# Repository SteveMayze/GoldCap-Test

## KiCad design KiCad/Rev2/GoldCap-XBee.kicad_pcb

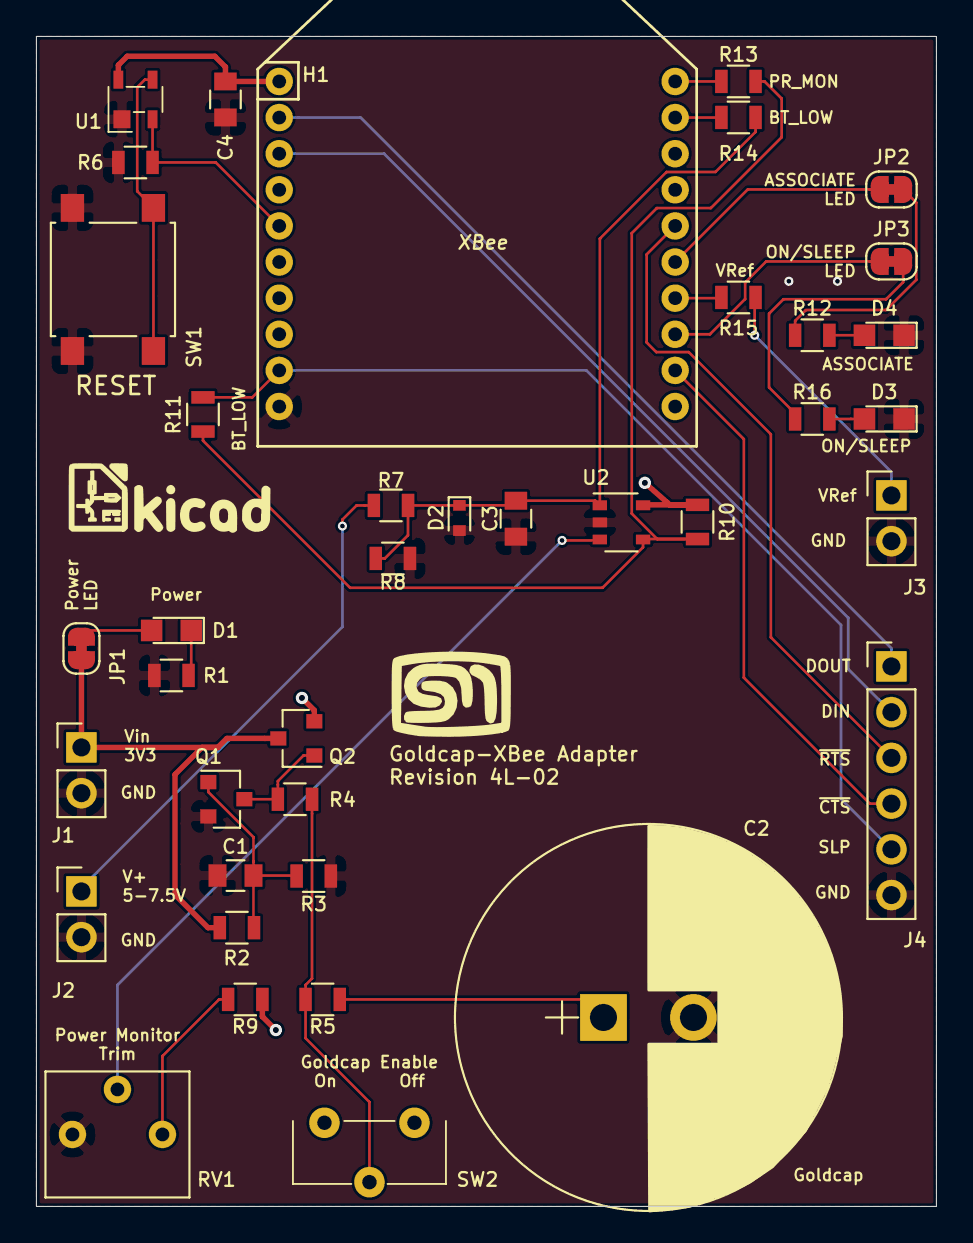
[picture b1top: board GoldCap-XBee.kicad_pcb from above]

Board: 4 copper layers, 50.0 x 65.0 mm, 39 parts (0 on the bottom side), 31 nets.

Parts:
C1, C3, C4: 100nF; C_0805
C2: 470mF 5V5; CP_Radial_D21.5mm_P5.00mm
D1, D3, D4: LED; LED_0805
D2: MM5Z3V3T1G; D_SOD-523
H1: DIGI_XBEE; XBEE_S2C
J1: 3V3 IN; Pin_Header_Straight_1x02_Pitch2.54mm
J2: 5-7.5V; Pin_Header_Straight_1x02_Pitch2.54mm
J3: VREF; Pin_Header_Straight_1x02_Pitch2.54mm
J4: Conn_01x06_Female; Pin_Header_Straight_1x06_Pitch2.54mm
JP1: Pwr LED; SolderJumper-2_P1.3mm_Bridged_RoundedPad1.0x1.5mm
JP2: ASSOCIATE_BR; SolderJumper-2_P1.3mm_Bridged_RoundedPad1.0x1.5mm
JP3: ON; SolderJumper-2_P1.3mm_Bridged_RoundedPad1.0x1.5mm
Q1: BC847; SOT-23
Q2: IRLML6401; SOT-23
R1, R12, R16: 680Ω; R_0805
R2: 470kΩ; R_0805
R3, R4, R6, R7, R8: 100kΩ; R_0805
R5: 33Ω; R_0805
R9, R11, R13, R14, R15: 0Ω; R_0805
R10: 10kΩ; R_0805
RV1: 10kΩ; Trimpot_CT6EP
SW1: Reset; SW_SPST_B3S-1000
SW2: SW_SPDT; SPST-CL-SB-12C01
U1: SGM811; SGM811B
U2: LMV331; SOT-25

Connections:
/ASSOCIATE: D4.2, R12.1
/ON: D3.2, R16.1
/PWR_MON: C3.1, D2.1, R7.2, R8.1, R14.1, U2.1
/SLEEP_REQ: H1.9, J4.5, R11.1
/VCC: C4.1, H1.1, Q2.2, R9.1, R10.1, SW2.1, U1.4, U2.5
/VIN_3V3: J1.1, JP1.1, Q2.3, R2.2
/VREF: J3.1, R15.1
/Vb: J2.1, R7.1
/Vref: RV1.2, U2.3
/XBEE_DIN: H1.3, J4.2
/XBEE_DOUT: H1.2, J4.1
/~BATT_LOW~: R10.2, R11.2, R13.1, U2.4
/~RESET: H1.5, R6.1, U1.2
/~XBEE_CTS: H1.12, J4.4
/~XBEE_RTS: H1.16, J4.3
GND: C1.2, C2.2, C3.2, C4.2, D2.2, D3.1, D4.1, H1.10, J1.2, J2.2, J3.2, J4.6, Q1.2, R1.2, R3.2, R6.2, R8.2, RV1.3, SW1.1, U1.1, U2.2
unnamed: C1.1, Q1.1, R2.1, R3.1
unnamed: C2.1, R5.2
unnamed: D1.1, R1.1
unnamed: D1.2, JP1.2
unnamed: H1.13, JP3.1
unnamed: H1.14, R15.2
unnamed: H1.15, JP2.1
unnamed: H1.19, R14.2
unnamed: H1.20, R13.2
unnamed: JP2.2, R12.2
unnamed: JP3.2, R16.2
unnamed: Q1.3, Q2.1, R4.1
unnamed: R4.2, R5.1, SW2.2
unnamed: R9.2, RV1.1
unnamed: SW1.2, U1.3

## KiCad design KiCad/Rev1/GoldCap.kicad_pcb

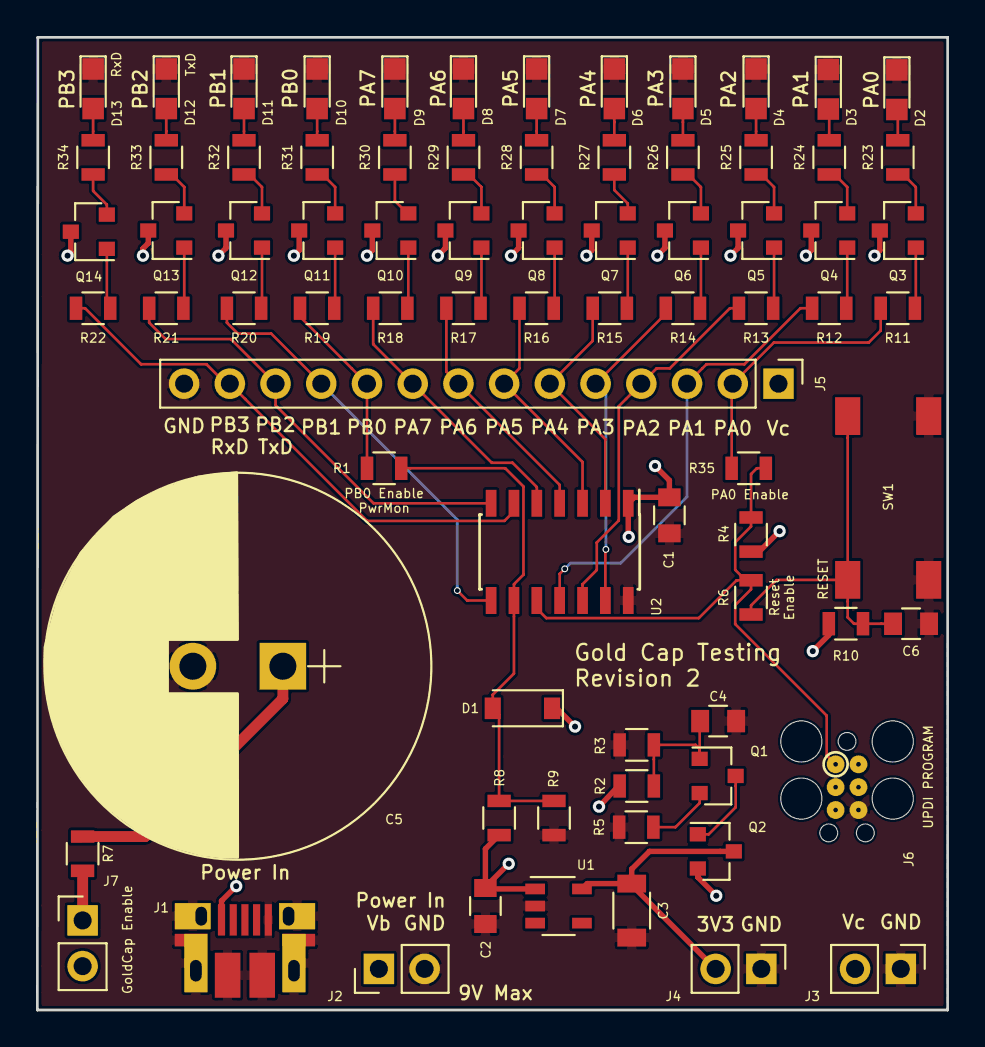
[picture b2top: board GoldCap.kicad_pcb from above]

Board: 2 copper layers, 50.6 x 54.0 mm, 78 parts (0 on the bottom side), 60 nets.

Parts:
C1, C4, C6: 100n; C_0805
C2: 1μF; C_0805
C3: 2.2μF; C_1206
C5: 470m 5V5; CP_Radial_D21.5mm_P5.00mm
D1: BAT43; D_SOD-123
D2, D3, D4, D5, D6, D7, D8, D9, D10, D11, D12, D13: LED; LED_0805
J1: USB_B_2.0_Micro
J2: Pwr In; Pin_Header_Straight_1x02_Pitch2.54mm
J3: Pwr Out; Pin_Header_Straight_1x02_Pitch2.54mm
J4, J7: Main Pwr; Pin_Header_Straight_1x02_Pitch2.54mm
J5: Conn_01x14_Male; Pin_Header_Straight_1x14_Pitch2.54mm
J6: Prog; PRG_TC2030-IDC-FP_TH
Q1, Q3, Q4, Q5, Q6, Q7, Q8, Q9, Q10, Q11, Q12, Q13, Q14: BC847; SOT-23
Q2: IRLML6401; SOT-23
R1, R6, R35: 0Ω; R_0805
R2: 100k; R_0805
R3, R10: 10k; R_0805
R4: 47kΩ; R_0805
R5: 100; R_0805
R7: 33; R_0805
R8: 68k; R_0805
R9: 27k; R_0805
R11, R12, R13, R14, R15, R16, R17, R18, R19, R20, R21, R22: 10kΩ; R_0805
R23, R24, R25, R26, R27, R28, R29, R30, R31, R32, R33, R34: 100Ω; R_0805
SW1: SW_TACTILE_SPST; SPST_FSM2JSMAA
U1: TPS70933DBV; SOT-23-5_TPS70933DBVR
U2: ATtiny1614-SS; SOIC-14_3.9x8.7mm_Pitch1.27mm

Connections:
/3V3: C3.1, J4.2, Q2.3, U1.5
/LED_A0: Q3.2, R23.1
/LED_A1: Q4.2, R24.1
/LED_A2: Q5.2, R25.1
/LED_A3: Q6.2, R26.1
/LED_A4: Q7.2, R27.1
/LED_A5: Q8.2, R28.1
/LED_A6: Q9.2, R29.1
/LED_A7: Q10.2, R30.1
/LED_B0: Q11.2, R31.1
/LED_B1: Q12.2, R32.1
/LED_B2: Q13.2, R33.1
/LED_B3: Q14.2, R34.1
/LED_PA0: J5.2, R11.2, R35.1
/LED_PA1: J5.3, R12.2, U2.11
/LED_PA2: J5.4, R13.2, U2.12
/LED_PA3: J5.5, R14.2, U2.13
/LED_PA4: J5.6, R15.2, U2.2
/LED_PA5: J5.7, R16.2, U2.3
/LED_PA6: J5.8, R17.2, U2.4
/LED_PA7: J5.9, R18.2, U2.5
/LED_PB0: J5.10, R1.2, R19.2
/LED_PB1: J5.11, R20.2, U2.8
/LED_PB2_TxD: J5.12, R21.2, U2.7
/LED_PB3_RxD: J5.13, R22.2, U2.6
/PDI_DATA: J6.1, R4.2, R6.2, R35.2, U2.10
/PwrMon: D1.2, R1.1, R8.2, R9.1, U2.9
/Vb: C2.1, J1.1, J2.1, R2.2, R8.1, U1.1
/Vc: C1.1, D1.1, J3.2, J5.1, J6.2, J7.2, Q2.2, Q3.3, Q4.3, Q5.3, Q6.3, Q7.3, Q8.3, Q9.3, Q10.3, Q11.3, Q12.3, Q13.3, Q14.3, R4.1, R10.1, U2.1
/~RESET: C6.1, R6.1, R10.2, SW1.1, SW1.2
GND: C1.2, C2.2, C3.2, C4.2, C5.2, C6.2, D2.1, D3.1, D4.1, D5.1, D6.1, D7.1, D8.1, D9.1, D10.1, D11.1, D12.1, D13.1, J1.5, J1.6, J2.2, J3.1, J4.1, J5.14, J6.6, R3.2, R5.2, R9.2, SW1.3, SW1.4, U1.2, U2.14
unnamed: C4.1, Q1.1, R2.1, R3.1
unnamed: C5.1, R7.2
unnamed: D2.2, R23.2
unnamed: D3.2, R24.2
unnamed: D4.2, R25.2
unnamed: D5.2, R26.2
unnamed: D6.2, R27.2
unnamed: D7.2, R28.2
unnamed: D8.2, R29.2
unnamed: D9.2, R30.2
unnamed: D10.2, R31.2
unnamed: D11.2, R32.2
unnamed: D12.2, R33.2
unnamed: D13.2, R34.2
unnamed: J7.1, R7.1
unnamed: Q1.2, R5.1
unnamed: Q1.3, Q2.1
unnamed: Q3.1, R11.1
unnamed: Q4.1, R12.1
unnamed: Q5.1, R13.1
unnamed: Q6.1, R14.1
unnamed: Q7.1, R15.1
unnamed: Q8.1, R16.1
unnamed: Q9.1, R17.1
unnamed: Q10.1, R18.1
unnamed: Q11.1, R19.1
unnamed: Q12.1, R20.1
unnamed: Q13.1, R21.1
unnamed: Q14.1, R22.1

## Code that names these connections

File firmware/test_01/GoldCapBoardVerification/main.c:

/*
 * GoldCapBoardVerification.c
 *
 * Created: 26/05/2019 19:31:06
 * Author : Steven
 */ 

#include <avr/io.h>
#include <util/delay.h>

int main(void)
{
	/*
		GPIO
			PA0 LED_PA0 (1)
			PA1 LED_PA1 (2)
			PA2 LED_PA2 (3)
			PA3 LED_PA3 (4)
			PA4 LED_PA4 (5)
			PA5 LED_PA5 (6)
			PA6 LED_PA6 (7)
			PA7 Power Monitor ( Analogue IN )

			PB0 TPI Clock
			PB1 TPI Data
			PB2 LED_PB2 (8)
			PB3 ~RESET

	*/
	DDRA |= ( 0x7F << PORTA0 );
	DDRA |= ( 0x00 << PORTA7 ); // Set port A7 as Input
	DDRB |= ( 1 << PORTB2);


	while (1) 
    {
		PORTA |= (0x7F << PORTA0 );
		PORTB |= ( 0x01 << PORTB2 );
		_delay_ms(1000);
		PORTA &= ~(0x7F << PORTA0 );
		PORTB &= ~( 0x01 << PORTB2 );
		_delay_ms(1000);
    }
}

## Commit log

2019-03-03 Fixed some zone fills
2019-03-05 Fixes some misplaced Vias and takes on upgrade to KiCad 5.0.2
2019-03-23 Stensils generated
2019-03-23 Correction to the castillations and zones
2019-03-23 Fixes the labelling and adds a breakout for the 3v3 line
2019-03-24 Created Rev 2 with the corrected GoldCap FP and a USB B Micro
2019-03-24 Adds the PRG/RUN jumper for programming in 5V
2019-03-27 Changes the handsolder 0805 to normal and neatens up labelling
2019-04-07 Changed the SOT-23_5 to reflect the datasheet
2019-04-07 Created the stencil file
2019-06-20 Revision 3 of the board plus new 3D elements
2019-06-20 Creates the pins for the capacitor as its own body
2019-06-22 Revision 3 final for OSHParch
2019-06-22 Removed unccessary C project files
2019-06-22 Updated the gitignore to exclude some C project files
2019-07-23 Fixed labelling and improve PwrMon isolation
2019-07-23 Adds the firmware for 1614
2019-07-23 Adds some doc
2019-07-23 Changes for gitignore for firmware
2019-07-25 Clean up of Debug and some corrections to the schematic
2019-07-29 Added some measurements to the schematic
2019-07-30 Simple changes to the test animation
2019-07-30 Temporary update of Atmel Studio files
2019-07-30 Adds an Atmel Start Solution for controlling the USART
2019-08-12 Initial checkin for Curiosity
2019-08-27 More experiements - The atmega4809 is a working starting point
2019-09-24 Implements the RTS from the XBee
2020-01-18 git ignore update
2020-03-04 some changes in getting a new revision organised
2020-03-23 Rev 2 of the dev board
2020-04-20 Clean up
2020-05-18 3d model changes
2020-05-18 Missing library
2020-05-18 Restored Footprint libraries
